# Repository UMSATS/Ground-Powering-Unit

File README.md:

# Ground-Powering-Unit
This is a repository to collaborate on the ground powering unit PCB for the UMSATS rocket.

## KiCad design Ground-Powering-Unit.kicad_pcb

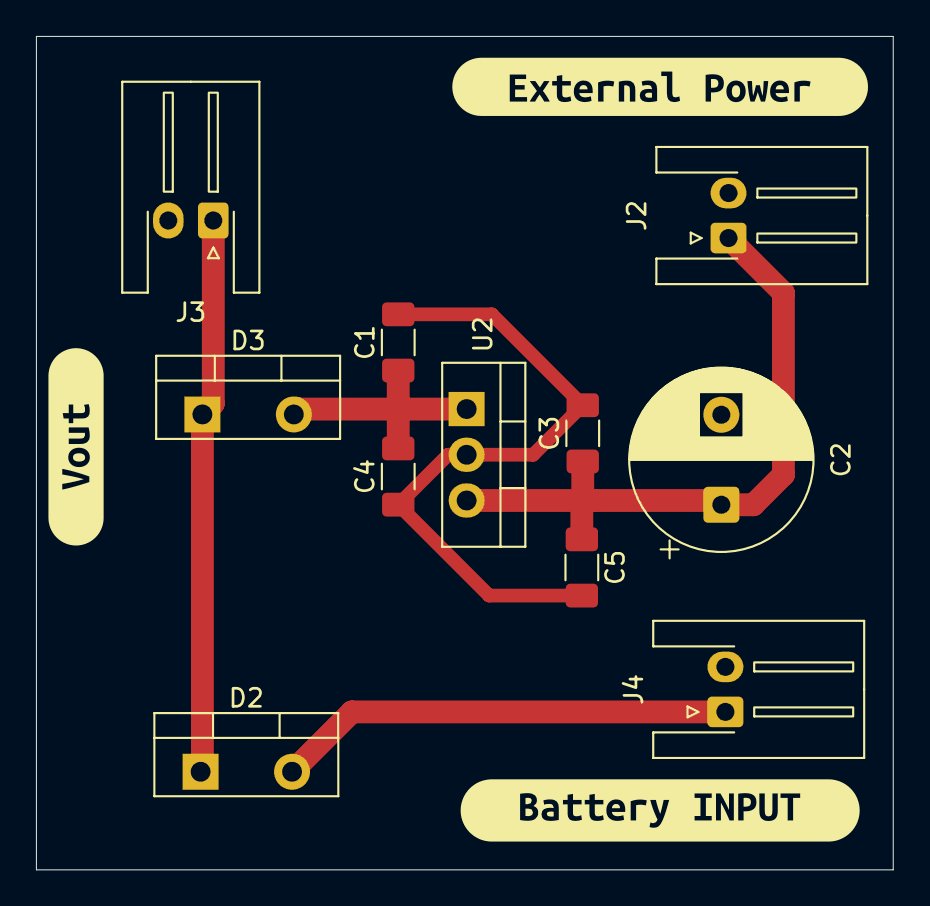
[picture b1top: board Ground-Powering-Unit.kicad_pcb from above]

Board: 2 copper layers, 47.6 x 46.3 mm, 14 parts (0 on the bottom side), 5 nets.

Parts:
C1, C3, C4, C5: 10uF; C_1206_3216Metric_Pad1.33x1.80mm_HandSolder
C2: 470uF; CP_Radial_D10.0mm_P5.00mm
D2, D3: MBR745; TO-220-2_Vertical
J2, J3, J4: Conn_01x02_Pin; JST_XH_S2B-XH-A-1_1x02_P2.50mm_Horizontal
U2: LF90_TO220; TO-220-3_Vertical
kibuzzard-6ACEBDE9: G***; kibuzzard-6ACEBDE9
kibuzzard-6ACEBE00: G***; kibuzzard-6ACEBE00
kibuzzard-6ACEBE29: G***; kibuzzard-6ACEBE29

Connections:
12V: C2.1, C3.1, C5.1, J2.1, U2.1 (VI)
/V1: C1.1, C4.1, D3.2 (A), U2.3 (VO)
GND: C1.2, C2.2, C3.2, C4.2, C5.2, J2.2, J3.2, J4.2, U2.2 (GND)
VBATT: D2.2 (A), J4.1
Vout: D2.1 (K), D3.1 (K), J3.1
